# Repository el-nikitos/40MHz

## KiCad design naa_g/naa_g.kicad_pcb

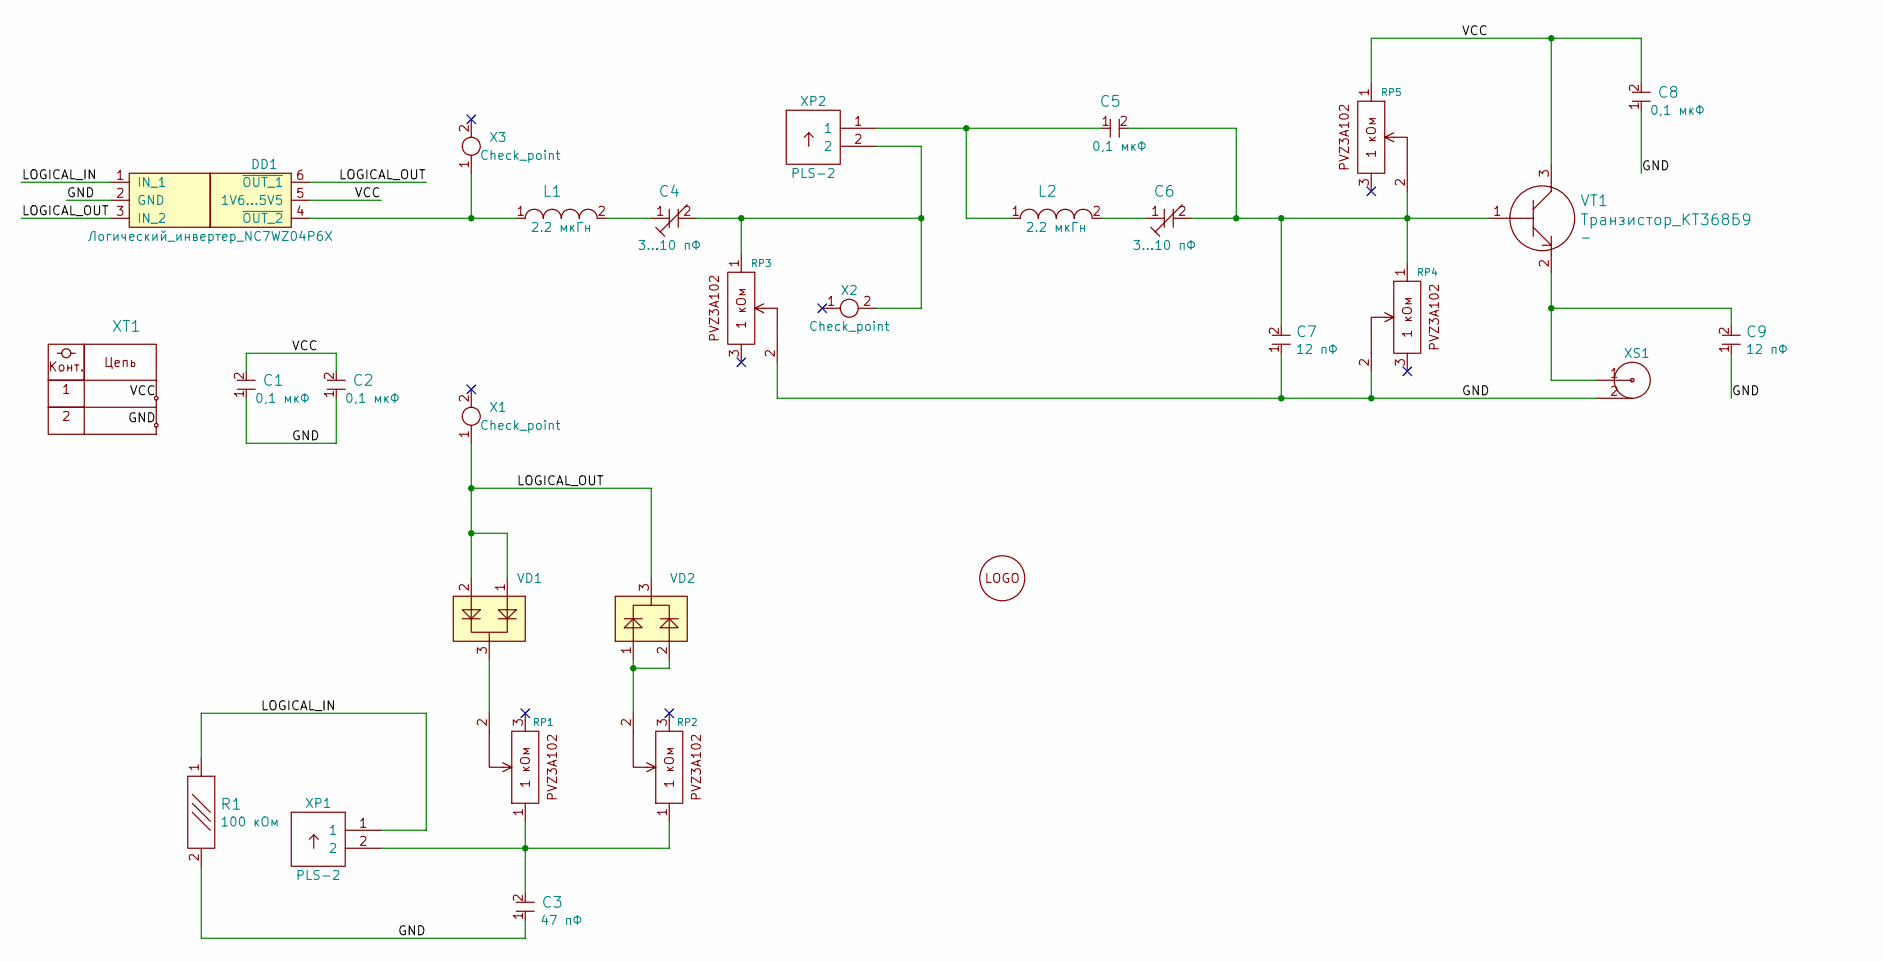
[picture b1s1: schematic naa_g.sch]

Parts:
C1, C2, C3, C5, C8: Конденсатор_16В_0.1_мкФ+-10проц.; Конденсатор_SMD_К10-83(0603)
C4, C6: Конденсатор_подстроечный_TZC3R100A110; Конденсатор_подстроечный_TZC3
C7, C9: Конденсатор_К10-83-50В-12_пФ+-10проц.-МП0; Конденсатор_SMD_К10-83(0603)
DD1: Логический_инвертер_NC7WZ04P6X; SC-70-6
L1, L2: Чип-индуктивность_2,2_мкГн±10%; Чип-индуктивность_SMD_0805
R1: Резистор_100_кОм±5%_0,1Вт; Резистор_SMD_0603-0,075_Вт
RP1, RP2, RP3, RP4, RP5: Резистор_подстроечный_PVA3A102; резистор_подстроечный_PVZ3A334
VD1, VD2: Набор_диодов_2Д803АС9; Корпус_КТ-46
VT1: Транзистор_КТ368Б9; Корпус_КТ-46
X1, X2, X3: Check_point; Пробник
X4: LOGO_NIKITOS_19х7; el-nikitos_19x7
XP1, XP2: Вилка_PLS-2; Вилка_PLS2_вертикальная
XS1: Розетка_KLS1-SMA001
XT1: Клеммник_х2; Клеммник_х2_шаг5

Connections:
/GND: C1.1, C2.1, C3.1, C7.1, C8.1, C9.1, DD1.2 (GND), R1.2, RP3.2, RP4.2, XS1.2, XT1.2
/LOGICAL_IN: DD1.1 (IN_1), R1.1, XP1.1
/LOGICAL_OUT: DD1.3 (IN_2), DD1.6 (~OUT_1), VD1.1, VD1.2, VD2.3, X1.1
/VCC: C1.2, C2.2, C8.2, DD1.5 (1V6...5V5), RP5.1, VT1.3, XT1.1
unnamed: C3.2, RP1.1, RP2.1, XP1.2
unnamed: C4.1, L1.2
unnamed: C4.2, RP3.1, X2.2, XP2.2
unnamed: C5.1, L2.1, XP2.1
unnamed: C5.2, C6.2, C7.2, RP4.1, RP5.2, VT1.1
unnamed: C6.1, L2.2
unnamed: C9.2, VT1.2, XS1.1
unnamed: DD1.4 (~OUT_2), L1.1, X3.1
unnamed: RP1.2, VD1.3
unnamed: RP2.2, VD2.1, VD2.2

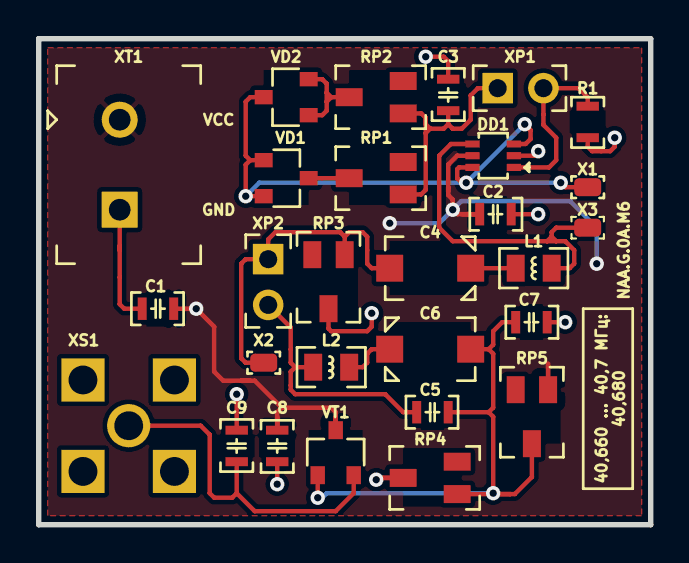
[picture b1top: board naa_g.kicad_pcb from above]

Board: 2 copper layers, 34.0 x 27.0 mm, 29 parts (1 on the bottom side), 14 nets.

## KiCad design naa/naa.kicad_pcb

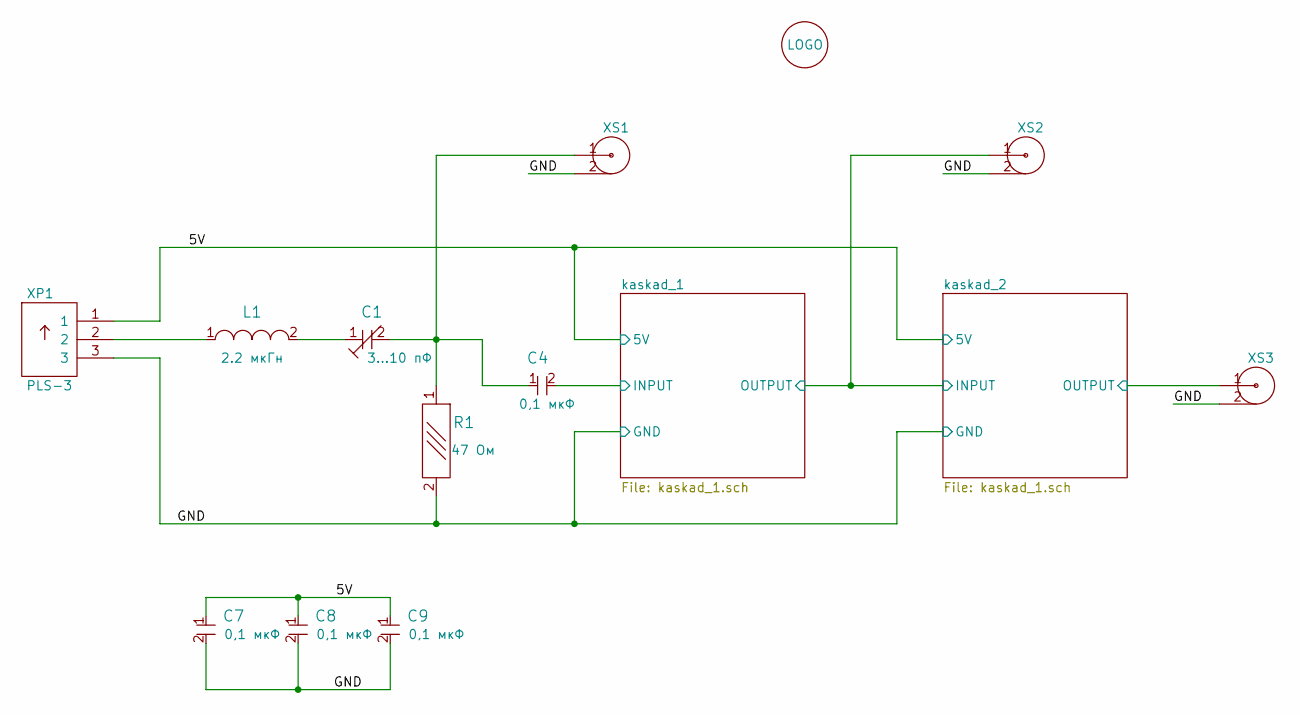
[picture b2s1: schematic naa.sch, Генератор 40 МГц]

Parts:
C1: Конденсатор_подстроечный_TZC3R100A110; Конденсатор_подстроечный_TZC3
C4, C7, C8, C9: Конденсатор_16В_0.1_мкФ+-10проц.; Конденсатор_SMD_К10-83(0603)
D1: LOGO; el-nikitos_19x7
L1: Чип-индуктивность_2,2_мкГн±10%; Чип-индуктивность_SMD_0805
R1: Резистор_47_Ом±5%_0,1Вт; Резистор_SMD_0603-0,075_Вт
XP1: Вилка_PLS-3; Вилка_PLS3_вертикальная
XS1, XS2, XS3: Розетка_KLS1-SMA001

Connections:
/5V: C7.1, C8.1, C9.1, XP1.1; also elsewhere on the board
/GND: C7.2, C8.2, C9.2, R1.2, XP1.3, XS1.2, XS2.2, XS3.2; also elsewhere on the board
/kaskad_1/INPUT: C4.2; also elsewhere on the board
/kaskad_2/INPUT: XS2.1; also elsewhere on the board
/kaskad_2/OUTPUT: XS3.1; also elsewhere on the board
unnamed: C1.1, L1.2
unnamed: C1.2, C4.1, R1.1, XS1.1
unnamed: L1.1, XP1.2

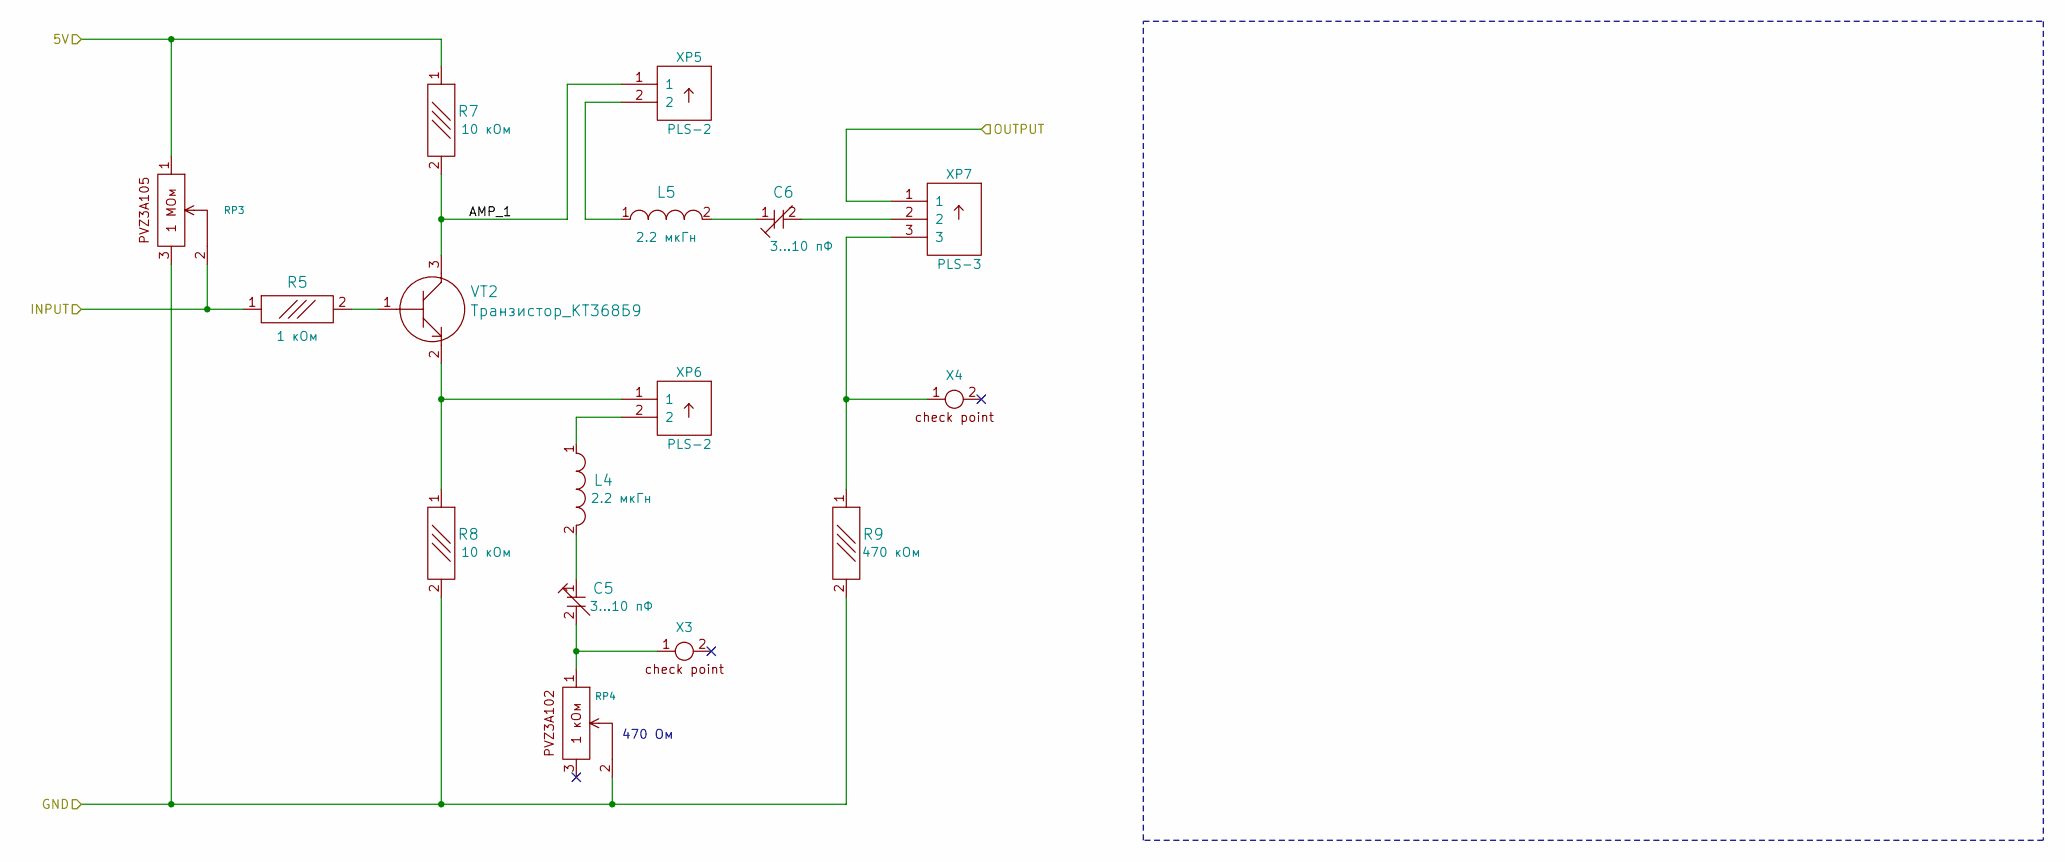
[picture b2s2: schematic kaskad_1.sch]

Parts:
C2, C3: Конденсатор_подстроечный_TZC3R100A110; Конденсатор_подстроечный_TZC3
L2, L3: Чип-индуктивность_2,2_мкГн±10%; Чип-индуктивность_SMD_0805
R2: Резистор_1_кОм±5%_0,1Вт; Резистор_SMD_0603-0,075_Вт
R3, R4: Резистор_10_кОм±5%_0,1Вт; Резистор_SMD_0603-0,075_Вт
R6: Резистор_470_Ом±5%_0,1Вт; Резистор_SMD_0603-0,075_Вт
RP1: Резистор_подстроечный_PVZ3A105; резистор_подстроечный_PVZ3A334
RP2: Резистор_подстроечный_PVA3A102; резистор_подстроечный_PVZ3A334
VT1: Транзистор_КТ368Б9; Корпус_КТ-46
X1, X2: Контрольная_точка_сопряжения; Пробник
XP2, XP3: Вилка_PLS-2; Вилка_PLS2_вертикальная
XP4: Вилка_PLS-3; Вилка_PLS3_вертикальная

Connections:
/5V: R3.1, RP1.1; also elsewhere on the board
/GND: R4.2, R6.2, RP1.3, RP2.2; also elsewhere on the board
/kaskad_1/AMP_1: R3.2, VT1.3, XP2.1
/kaskad_1/INPUT: R2.1, RP1.2; also elsewhere on the board
/kaskad_2/INPUT: XP4.1; also elsewhere on the board
unnamed: C2.1, L2.2
unnamed: C2.2, RP2.1, X1.1
unnamed: C3.1, L3.2
unnamed: C3.2, XP4.2
unnamed: L2.1, XP3.2
unnamed: L3.1, XP2.2
unnamed: R2.2, VT1.1
unnamed: R4.1, VT1.2, XP3.1
unnamed: R6.1, X2.1, XP4.3

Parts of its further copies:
C5, C6: Конденсатор_подстроечный_TZC3R100A110; Конденсатор_подстроечный_TZC3
L4, L5: Чип-индуктивность_2,2_мкГн±10%; Чип-индуктивность_SMD_0805
R5: Резистор_1_кОм±5%_0,1Вт; Резистор_SMD_0603-0,075_Вт
R7, R8: Резистор_10_кОм±5%_0,1Вт; Резистор_SMD_0603-0,075_Вт
R9: Резистор_470_Ом±5%_0,1Вт; Резистор_SMD_0603-0,075_Вт
RP3: Резистор_подстроечный_PVZ3A105; резистор_подстроечный_PVZ3A334
RP4: Резистор_подстроечный_PVA3A102; резистор_подстроечный_PVZ3A334
VT2: Транзистор_КТ368Б9; Корпус_КТ-46
X3, X4: Контрольная_точка_сопряжения; Пробник
XP5, XP6: Вилка_PLS-2; Вилка_PLS2_вертикальная
XP7: Вилка_PLS-3; Вилка_PLS3_вертикальная

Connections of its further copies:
/5V: R7.1, RP3.1; also elsewhere on the board
/GND: R8.2, R9.2, RP3.3, RP4.2; also elsewhere on the board
/kaskad_2/AMP_1: R7.2, VT2.3, XP5.1
/kaskad_2/INPUT: R5.1, RP3.2; also elsewhere on the board
/kaskad_2/OUTPUT: XP7.1; also elsewhere on the board
unnamed: C5.1, L4.2
unnamed: C5.2, RP4.1, X3.1
unnamed: C6.1, L5.2
unnamed: C6.2, XP7.2
unnamed: L4.1, XP6.2
unnamed: L5.1, XP5.2
unnamed: R5.2, VT2.1
unnamed: R8.1, VT2.2, XP6.1
unnamed: R9.1, X4.1, XP7.3

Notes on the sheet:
470 Ом

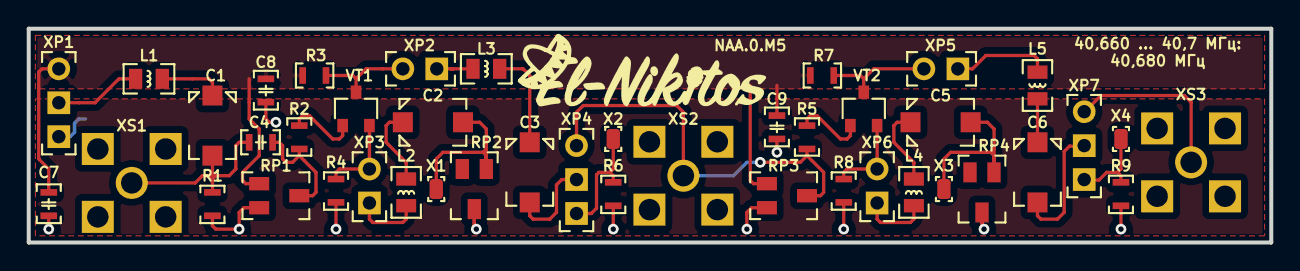
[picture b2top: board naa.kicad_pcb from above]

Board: 2 copper layers, 93.0 x 16.0 mm, 44 parts (0 on the bottom side), 28 nets.

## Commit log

2020-05-19 создан проект генератора на 40 МГц
2020-05-24 схема одного каскада
2020-05-24 готова схема, добавлены gerber и pdf
2020-05-25 добавлены кондеи на питание, обновлены gerber и pdf
2020-06-19 gerber-ы заказа, модель генератора на логическом инверторе
2020-06-21 подготовлен проект и GERBER платы генератора на логическом инверторе
2020-08-08 обновлена PDF
